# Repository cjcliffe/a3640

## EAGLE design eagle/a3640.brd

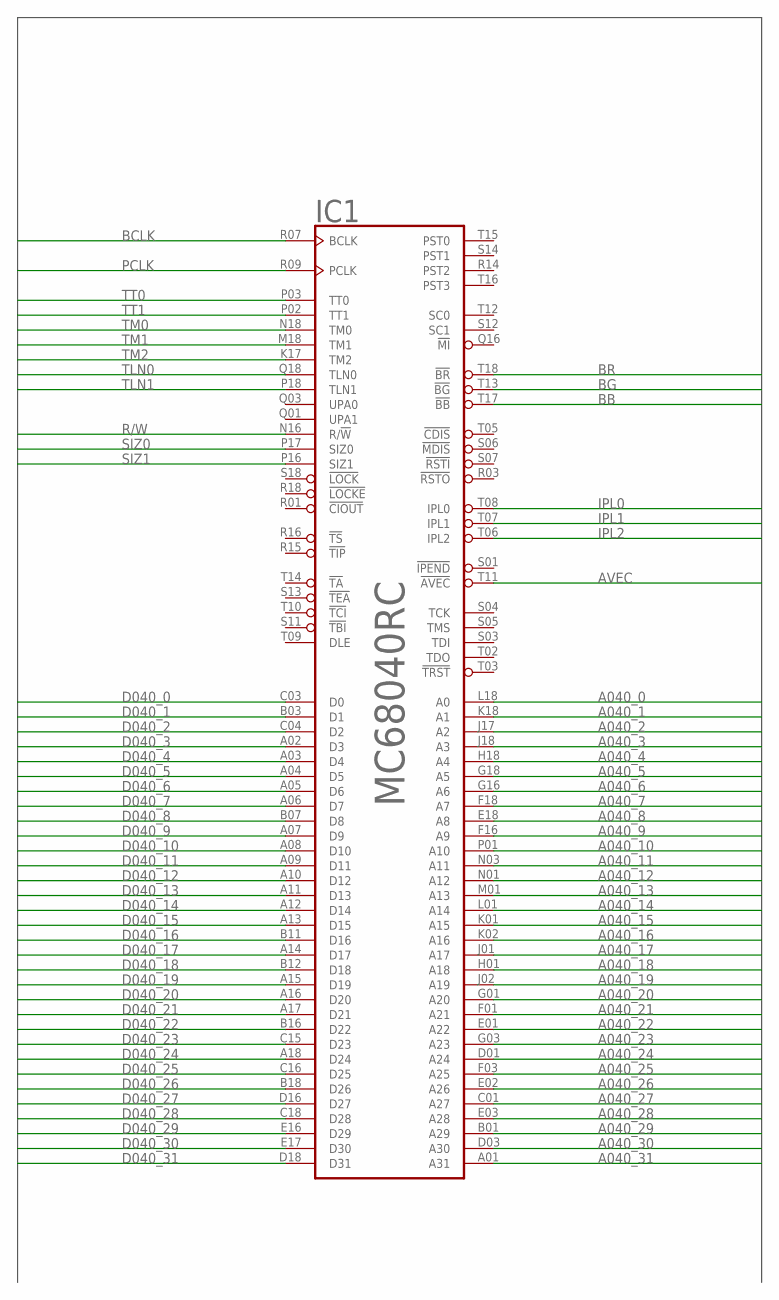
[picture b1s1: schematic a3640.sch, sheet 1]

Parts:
IC1: MC68040RC; MPGA-179

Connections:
A040_0: IC1.L18 (A0)
A040_1: IC1.K18 (A1)
A040_2: IC1.J17 (A2)
A040_3: IC1.J18 (A3)
A040_4: IC1.H18 (A4)
A040_5: IC1.G18 (A5)
A040_6: IC1.G16 (A6)
A040_7: IC1.F18 (A7)
A040_8: IC1.E18 (A8)
A040_9: IC1.F16 (A9)
A040_10: IC1.P01 (A10)
A040_11: IC1.N03 (A11)
A040_12: IC1.N01 (A12)
A040_13: IC1.M01 (A13)
A040_14: IC1.L01 (A14)
A040_15: IC1.K01 (A15)
A040_16: IC1.K02 (A16)
A040_17: IC1.J01 (A17)
A040_18: IC1.H01 (A18)
A040_19: IC1.J02 (A19)
A040_20: IC1.G01 (A20)
A040_21: IC1.F01 (A21)
A040_22: IC1.E01 (A22)
A040_23: IC1.G03 (A23)
A040_24: IC1.D01 (A24)
A040_25: IC1.F03 (A25)
A040_26: IC1.E02 (A26)
A040_27: IC1.C01 (A27)
A040_28: IC1.E03 (A28)
A040_29: IC1.B01 (A29)
A040_30: IC1.D03 (A30)
A040_31: IC1.A01 (A31)
AVEC: IC1.T11 (!AVEC)
BB: IC1.T17 (!BB)
BCLK: IC1.R07 (BCLK)
BG: IC1.T13 (!BG)
BR: IC1.T18 (!BR)
D040_0: IC1.C03 (D0); also elsewhere on the board
D040_1: IC1.B03 (D1); also elsewhere on the board
D040_2: IC1.C04 (D2); also elsewhere on the board
D040_3: IC1.A02 (D3); also elsewhere on the board
D040_4: IC1.A03 (D4); also elsewhere on the board
D040_5: IC1.A04 (D5); also elsewhere on the board
D040_6: IC1.A05 (D6); also elsewhere on the board
D040_7: IC1.A06 (D7); also elsewhere on the board
D040_8: IC1.B07 (D8); also elsewhere on the board
D040_9: IC1.A07 (D9); also elsewhere on the board
D040_10: IC1.A08 (D10); also elsewhere on the board
D040_11: IC1.A09 (D11); also elsewhere on the board
D040_12: IC1.A10 (D12); also elsewhere on the board
D040_13: IC1.A11 (D13); also elsewhere on the board
D040_14: IC1.A12 (D14); also elsewhere on the board
D040_15: IC1.A13 (D15); also elsewhere on the board
D040_16: IC1.B11 (D16); also elsewhere on the board
D040_17: IC1.A14 (D17); also elsewhere on the board
D040_18: IC1.B12 (D18); also elsewhere on the board
D040_19: IC1.A15 (D19); also elsewhere on the board
D040_20: IC1.A16 (D20); also elsewhere on the board
D040_21: IC1.A17 (D21); also elsewhere on the board
D040_22: IC1.B16 (D22); also elsewhere on the board
D040_23: IC1.C15 (D23); also elsewhere on the board
D040_24: IC1.A18 (D24); also elsewhere on the board
D040_25: IC1.C16 (D25); also elsewhere on the board
D040_26: IC1.B18 (D26); also elsewhere on the board
D040_27: IC1.D16 (D27); also elsewhere on the board
D040_28: IC1.C18 (D28); also elsewhere on the board
D040_29: IC1.E16 (D29); also elsewhere on the board
D040_30: IC1.E17 (D30); also elsewhere on the board
D040_31: IC1.D18 (D31); also elsewhere on the board
GND: IC1.B02 (GND), IC1.B04 (GND), IC1.B06 (GND), IC1.B08 (GND), IC1.B10 (GND), IC1.B13 (GND), IC1.B15 (GND), IC1.B17 (GND), IC1.C06 (GND), IC1.C07 (GND), IC1.C09 (GND), IC1.C11 (GND), IC1.C13 (GND), IC1.D02 (GND), IC1.D17 (GND), IC1.F02 (GND), IC1.F17 (GND), IC1.H02 (GND), IC1.H17 (GND), IC1.K03 (GND), IC1.K16 (GND), IC1.L02 (GND), IC1.L03 (GND), IC1.L17 (GND), IC1.M16 (GND), IC1.N02 (GND), IC1.N17 (GND), IC1.Q02 (GND), IC1.Q17 (GND), IC1.R04 (GND), IC1.R06 (GND), IC1.R10 (GND), IC1.R11 (GND), IC1.R13 (GND), IC1.S02 (GND), IC1.S09 (GND), IC1.S10 (GND), IC1.S15 (GND), IC1.S17 (GND), IC1.T04 (GND); also elsewhere on the board
IPL0: IC1.T08 (IPL0)
IPL1: IC1.T07 (IPL1)
IPL2: IC1.T06 (IPL2)
PCLK: IC1.R09 (PCLK)
R/W: IC1.N16 (R/!W)
SIZ0: IC1.P17 (SIZ0)
SIZ1: IC1.P16 (SIZ1)
TLN0: IC1.Q18 (TLN0)
TLN1: IC1.P18 (TLN1)
TM0: IC1.N18 (TM0)
TM1: IC1.M18 (TM1)
TM2: IC1.K17 (TM2)
TT0: IC1.P03 (TT0)
TT1: IC1.P02 (TT1)
VCC: IC1.B05 (VCC), IC1.B09 (VCC), IC1.B14 (VCC), IC1.C02 (VCC), IC1.C05 (VCC), IC1.C08 (VCC), IC1.C10 (VCC), IC1.C12 (VCC), IC1.C14 (VCC), IC1.C17 (VCC), IC1.G02 (VCC), IC1.G17 (VCC), IC1.H03 (VCC), IC1.H16 (VCC), IC1.J03 (VCC), IC1.J16 (VCC), IC1.L16 (VCC), IC1.M02 (VCC), IC1.M03 (VCC), IC1.M17 (VCC), IC1.R02 (VCC), IC1.R05 (VCC), IC1.R08 (VCC), IC1.R12 (VCC), IC1.R17 (VCC), IC1.S08 (VCC), IC1.S16 (VCC); also elsewhere on the board

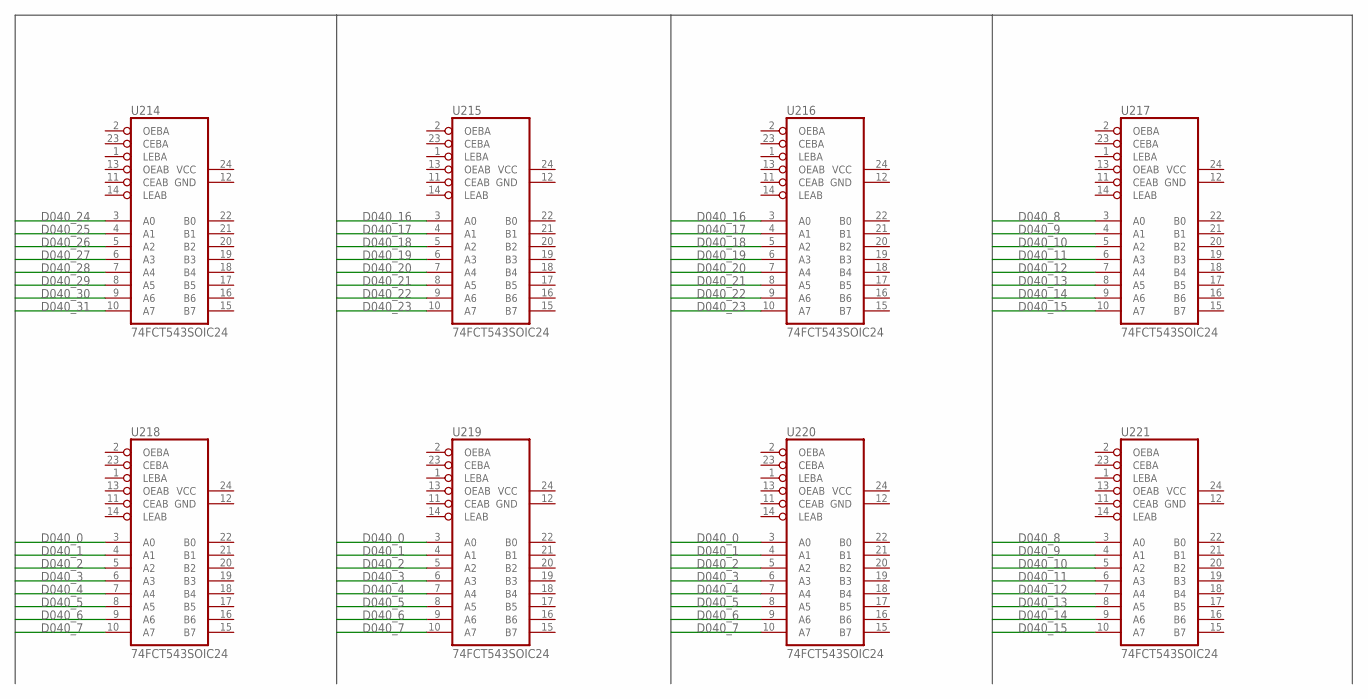
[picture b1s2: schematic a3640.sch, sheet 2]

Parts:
U214, U215, U216, U217, U218, U219, U220, U221: 74FCT543SOIC24; 74FCT543A

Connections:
D040_0: U218.3 (A0), U219.3 (A0), U220.3 (A0); also elsewhere on the board
D040_1: U218.4 (A1), U219.4 (A1), U220.4 (A1); also elsewhere on the board
D040_2: U218.5 (A2), U219.5 (A2), U220.5 (A2); also elsewhere on the board
D040_3: U218.6 (A3), U219.6 (A3), U220.6 (A3); also elsewhere on the board
D040_4: U218.7 (A4), U219.7 (A4), U220.7 (A4); also elsewhere on the board
D040_5: U218.8 (A5), U219.8 (A5), U220.8 (A5); also elsewhere on the board
D040_6: U218.9 (A6), U219.9 (A6), U220.9 (A6); also elsewhere on the board
D040_7: U218.10 (A7), U219.10 (A7), U220.10 (A7); also elsewhere on the board
D040_8: U217.3 (A0), U221.3 (A0); also elsewhere on the board
D040_9: U217.4 (A1), U221.4 (A1); also elsewhere on the board
D040_10: U217.5 (A2), U221.5 (A2); also elsewhere on the board
D040_11: U217.6 (A3), U221.6 (A3); also elsewhere on the board
D040_12: U217.7 (A4), U221.7 (A4); also elsewhere on the board
D040_13: U217.8 (A5), U221.8 (A5); also elsewhere on the board
D040_14: U217.9 (A6), U221.9 (A6); also elsewhere on the board
D040_15: U217.10 (A7), U221.10 (A7); also elsewhere on the board
D040_16: U215.3 (A0), U216.3 (A0); also elsewhere on the board
D040_17: U215.4 (A1), U216.4 (A1); also elsewhere on the board
D040_18: U215.5 (A2), U216.5 (A2); also elsewhere on the board
D040_19: U215.6 (A3), U216.6 (A3); also elsewhere on the board
D040_20: U215.7 (A4), U216.7 (A4); also elsewhere on the board
D040_21: U215.8 (A5), U216.8 (A5); also elsewhere on the board
D040_22: U215.9 (A6), U216.9 (A6); also elsewhere on the board
D040_23: U215.10 (A7), U216.10 (A7); also elsewhere on the board
D040_24: U214.3 (A0); also elsewhere on the board
D040_25: U214.4 (A1); also elsewhere on the board
D040_26: U214.5 (A2); also elsewhere on the board
D040_27: U214.6 (A3); also elsewhere on the board
D040_28: U214.7 (A4); also elsewhere on the board
D040_29: U214.8 (A5); also elsewhere on the board
D040_30: U214.9 (A6); also elsewhere on the board
D040_31: U214.10 (A7); also elsewhere on the board
GND: U214.12 (GND), U215.12 (GND), U216.12 (GND), U217.12 (GND), U218.12 (GND), U219.12 (GND), U220.12 (GND), U221.12 (GND); also elsewhere on the board
VCC: U214.24 (VCC), U215.24 (VCC), U216.24 (VCC), U217.24 (VCC), U218.24 (VCC), U219.24 (VCC), U220.24 (VCC), U221.24 (VCC); also elsewhere on the board

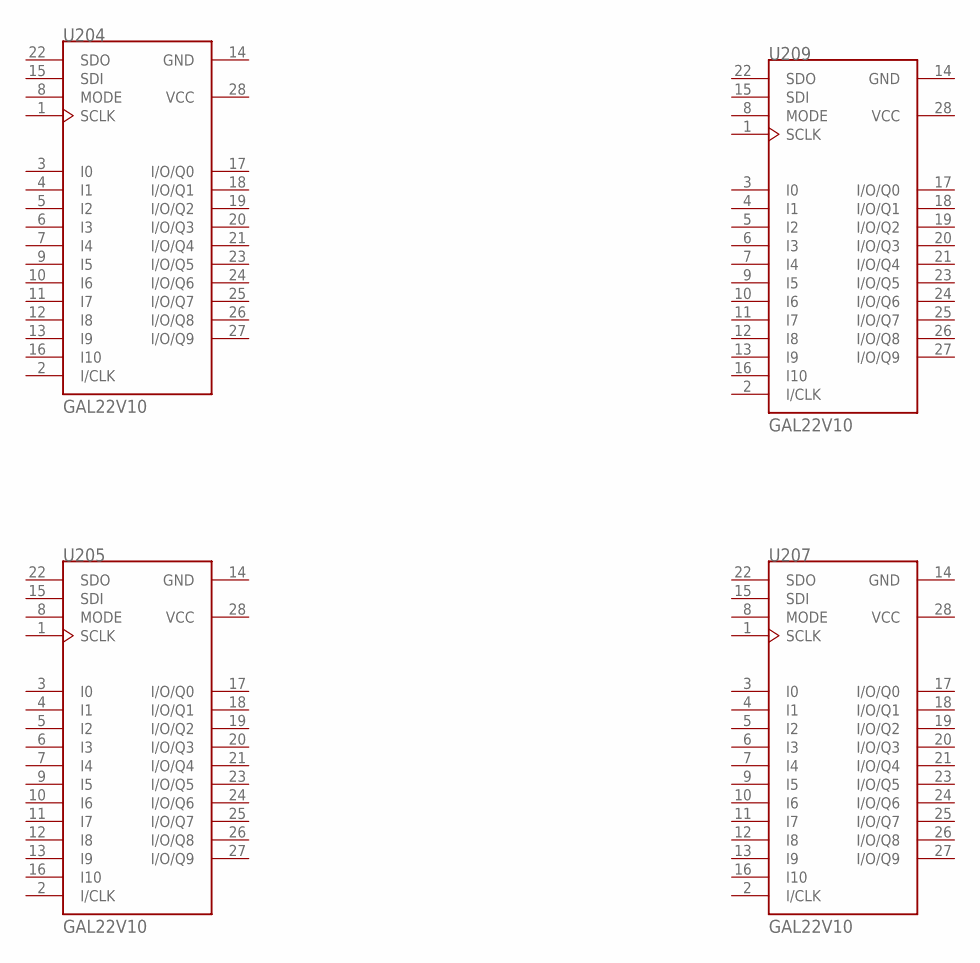
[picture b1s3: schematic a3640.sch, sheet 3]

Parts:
U204, U205, U207, U209: GAL22V10

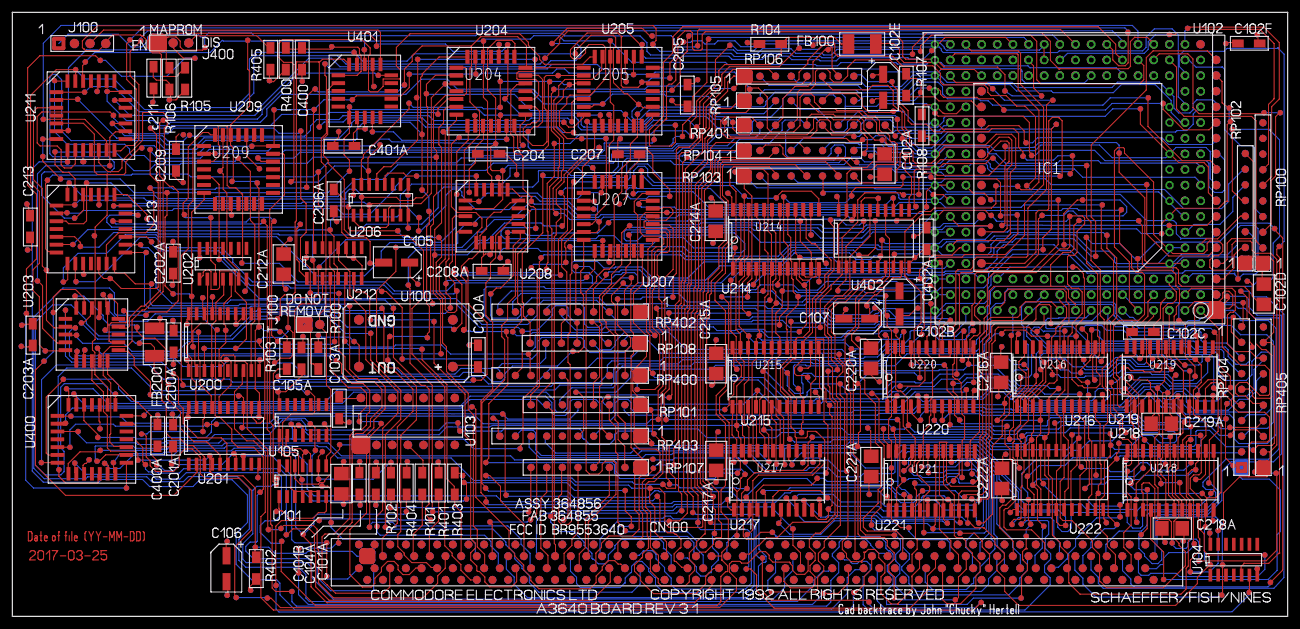
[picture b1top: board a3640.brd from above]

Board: 4 copper layers, 207.0 x 98.0 mm, 13 parts (0 on the bottom side), 34 nets.

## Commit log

2017-03-26 Basic import of John's data.
2017-03-28 placed an 040 part and wired up the data/address buses to a net.
2017-03-29 chipping away at the schematic
2017-03-30 More stuff.
2017-03-30 Create lib
2017-03-30 Add files via upload
    Originals schematics of the a3640 batch in production.
2017-03-30 footprint update and parts placement
